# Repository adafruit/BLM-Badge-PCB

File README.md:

# BLM-Badge-PCB

Black Lives Matter interactive electronic learning kit.

https://www.adafruit.com/blacklivesmatter

CAD files are released under Public Domain

https://creativecommons.org/share-your-work/public-domain/

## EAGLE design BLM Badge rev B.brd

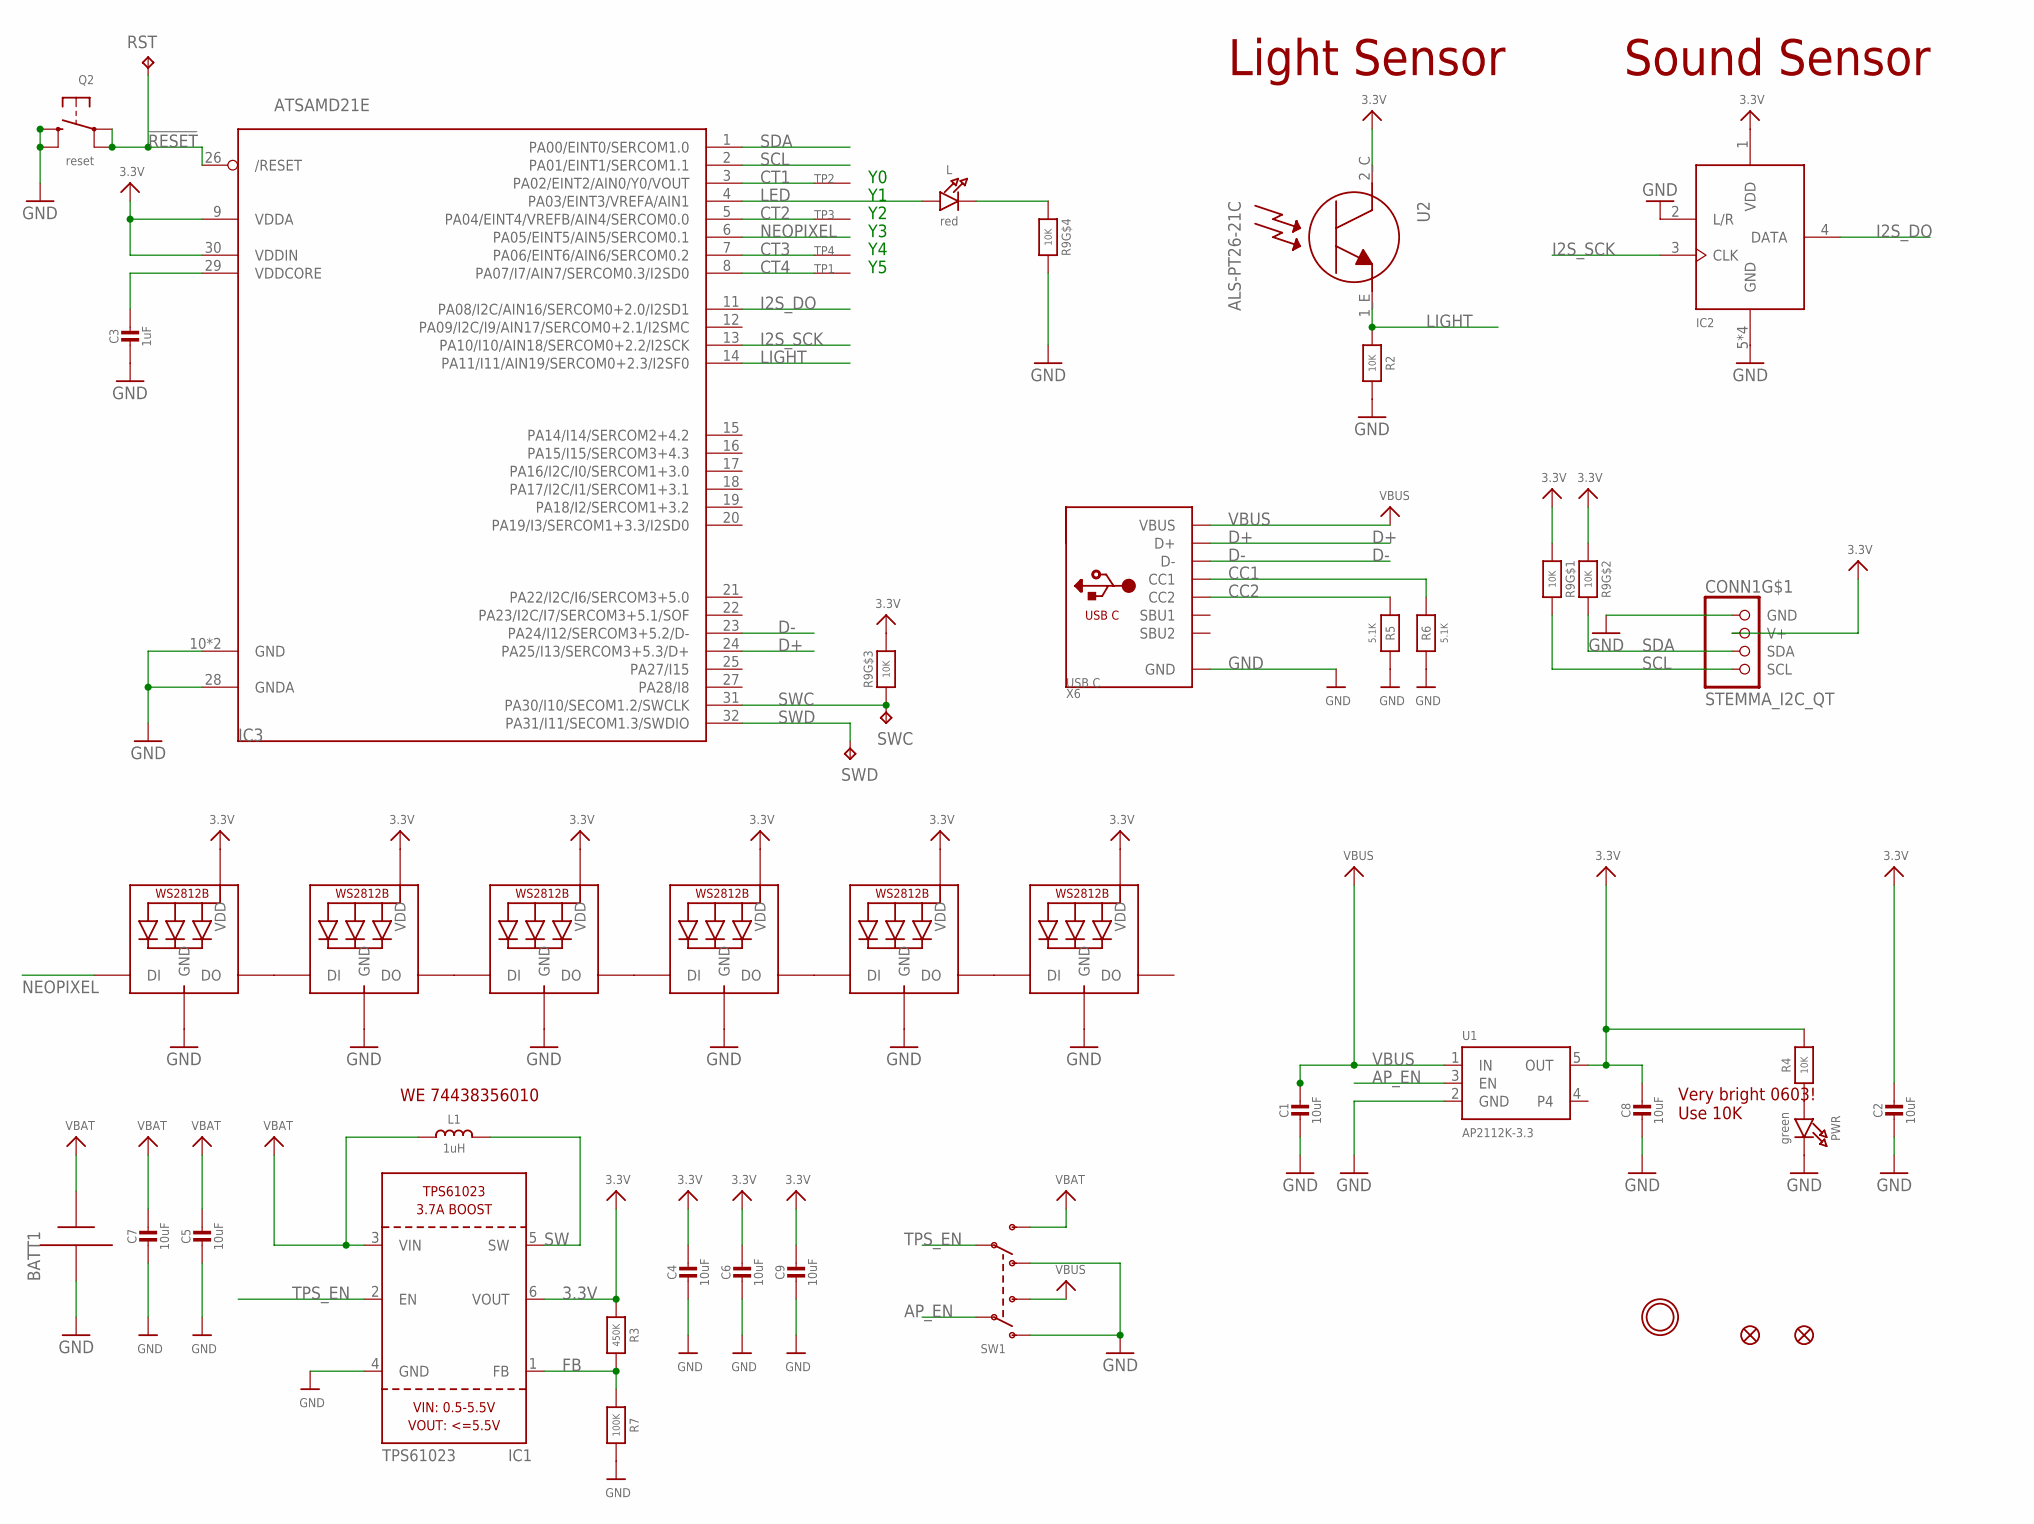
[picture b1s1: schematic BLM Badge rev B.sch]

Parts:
BATT1: BATTERYHOLDER_2XAAA; 2XAAA
C1, C2, C4, C5, C6, C7, C8, C9: 10uF; 0805-NO
C3: 1uF; 0603-NO
CONN1: STEMMA_I2C_QT; JST_SH4
FID1, FID2: FIDUCIAL_1MM
IC1: TPS61023; SOT563
IC2: MIC_PDM; SPK0415HM4H
IC3: ATSAMD21E; QFN32_5MM
L: red; CHIPLED_0603_NOOUTLINE
L1: 1uH; INDUCTOR_5X5MM_TDK_VLC5045
LED2, LED3, LED4, LED5, LED6, LED7: WS2812B_4020
PWR: green; CHIPLED_0603_NOOUTLINE
Q2: reset; BTN_KMR2_4.6X2.8
R2, R4: 10K; 0603-NO
R3: 450K; 0603-NO
R5, R6: 5.1K; 0603-NO
R7: 100K; 0603-NO
R9: 10K; RESPACK_4X0603
RST: TPTP17R; TP17R
SW1: SWITCH_DPDTEG1390; EG1390
SWC: TPTP17R; TP17R
SWD: TPTP17R; TP17R
TP1, TP2, TP3, TP4: SEWTAPPCB_ALLIGATOR; PCB_ALLI
U1: AP2112K-3.3; SOT23-5
U2: ALS-PT26-21C
U$33: MOUNTINGHOLE3.0THIN; MOUNTINGHOLE_3.0_PLATEDTHIN
X6: USB C; USB_C_CUSB31-CFM2AX-01-X

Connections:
3.3V: C2.1, C4.1, C6.1, C8.1, C9.1, CONN1.2 (V+), IC1.6 (VOUT), IC2.1 (VDD), IC3.9 (VDDA), IC3.30 (VDDIN), LED2.2 (VDD), LED3.2 (VDD), LED4.2 (VDD), LED5.2 (VDD), LED6.2 (VDD), LED7.2 (VDD), R3.1, R4.2, R9.1, R9.2 (1), R9.6 (2), U1.5 (OUT), U2.2_C (C)
!RESET: IC3.26 (/RESET), Q2.A, Q2.A' (P1), RST.TP
AP_EN: SW1.P1, U1.3 (EN)
CC1: R6.2, X6.A5 (CC1)
CC2: R5.2, X6.B5 (CC2)
CT1: IC3.3 (PA02/EINT2/AIN0/Y0/VOUT), TP2.P$1
CT2: IC3.5 (PA04/EINT4/VREFB/AIN4/SERCOM0.0), TP3.P$1
CT3: IC3.7 (PA06/EINT6/AIN6/SERCOM0.2), TP4.P$1
CT4: IC3.8 (PA07/I7/AIN7/SERCOM0.3/I2SD0), TP1.P$1
D+: IC3.24 (PA25/I13/SERCOM3+5.3/D+), X6.A6 (D+), X6.B6 (D+)
D-: IC3.23 (PA24/I12/SERCOM3+5.2/D-), X6.A7 (D-), X6.B7 (D-)
FB: IC1.1 (FB), R3.2, R7.1
GND: BATT1.MINUS (-), C1.2, C2.2, C3.2, C4.2, C5.2, C6.2, C7.2, C8.2, C9.2, CONN1.1 (GND), IC1.4 (GND), IC2.2 (L/R), IC2.5 (GND), IC2.6 (GND), IC2.7 (GND), IC2.8 (GND), IC3.10 (GND), IC3.28 (GNDA), IC3.33 (GND), LED2.4 (GND), LED3.4 (GND), LED4.4 (GND), LED5.4 (GND), LED6.4 (GND), LED7.4 (GND), PWR.C, Q2.B (S), Q2.B' (S1), R2.1, R5.1, R6.1, R7.2, R9.5 (2), SW1.O1, SW1.O2, U1.2 (GND), X6.A1B12 (GND), X6.B1A12 (GND)
I2S_DO: IC2.4 (DATA), IC3.11 (PA08/I2C/AIN16/SERCOM0+2.0/I2SD1)
I2S_SCK: IC2.3 (CLK), IC3.13 (PA10/I10/AIN18/SERCOM0+2.2/I2SCK)
LED: IC3.4 (PA03/EINT3/VREFA/AIN1), L.A
LIGHT: IC3.14 (PA11/I11/AIN19/SERCOM0+2.3/I2SF0), R2.2, U2.1_E (E)
unnamed: L.C, R9.4 (1)
unnamed: PWR.A, R4.1
unnamed: LED2.3 (DO), LED3.1 (DI)
unnamed: LED3.3 (DO), LED4.1 (DI)
unnamed: LED4.3 (DO), LED5.1 (DI)
unnamed: LED6.3 (DO), LED7.1 (DI)
unnamed: LED5.3 (DO), LED6.1 (DI)
NEOPIXEL: IC3.6 (PA05/EINT5/AIN5/SERCOM0.1), LED2.1 (DI)
SCL: CONN1.4 (SCL), IC3.2 (PA01/EINT1/SERCOM1.1), R9.8 (2)
SDA: CONN1.3 (SDA), IC3.1 (PA00/EINT0/SERCOM1.0), R9.7 (2)
SW: IC1.5 (SW), L1.P$2 (2)
SWC: IC3.31 (PA30/I10/SECOM1.2/SWCLK), R9.3 (1), SWC.TP
SWD: IC3.32 (PA31/I11/SECOM1.3/SWDIO), SWD.TP
TPS_EN: IC1.2 (EN), SW1.P2
VBAT: BATT1.PLUS (+), C5.1, C7.1, IC1.3 (VIN), L1.P$1 (1), SW1.S2
VBUS: C1.1, SW1.S1, U1.1 (IN), X6.A4B9 (VBUS), X6.B4A9 (VBUS)
VDDCORE: C3.1, IC3.29 (VDDCORE)

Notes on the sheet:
Very bright 0603! Use 10K
WE 74438356010
Sound Sensor
Light Sensor

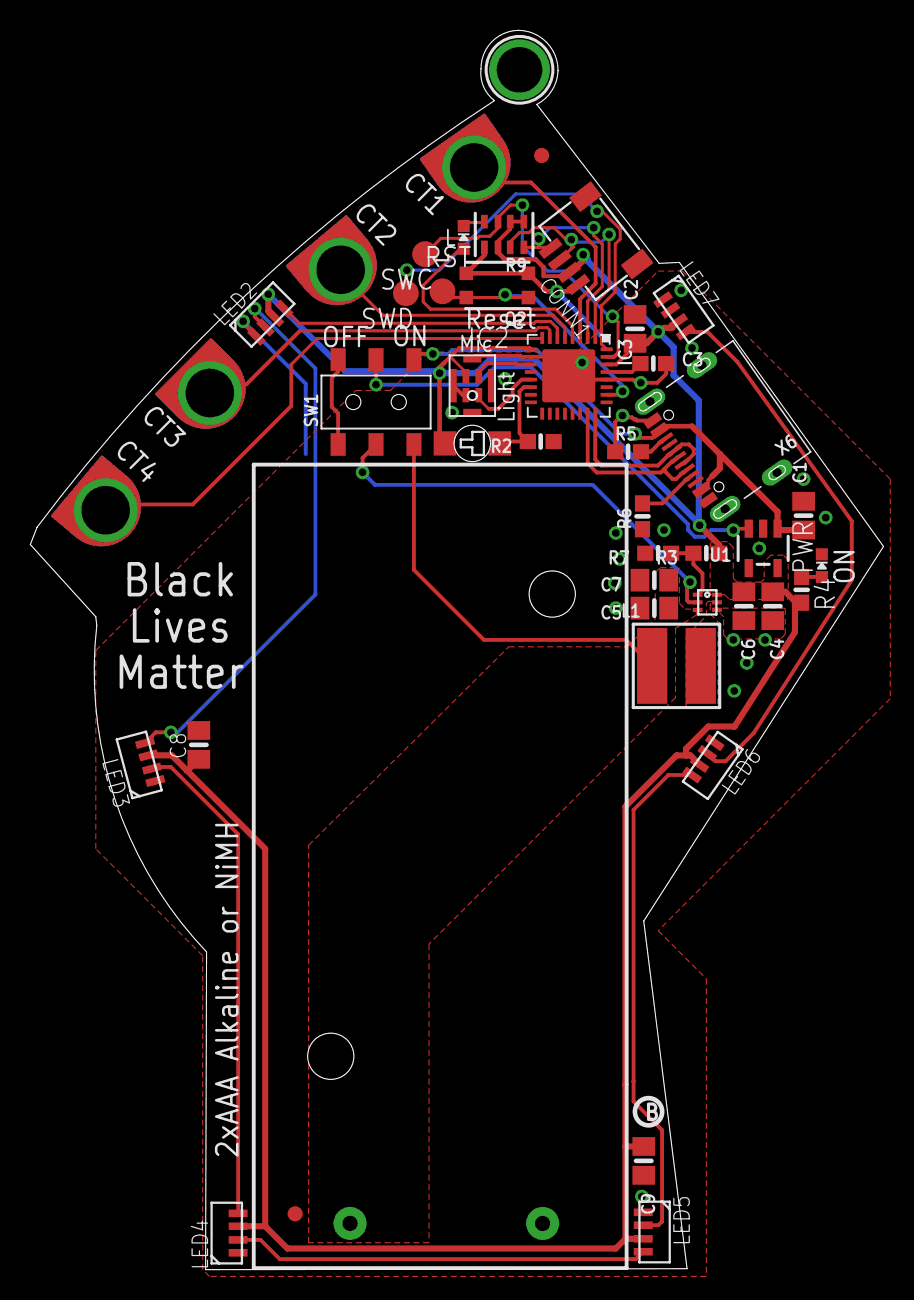
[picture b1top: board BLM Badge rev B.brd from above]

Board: 2 copper layers, 56.3 x 81.7 mm, 47 parts (1 on the bottom side), 34 nets.

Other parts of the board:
U$1: BLM_FRONT
U$40: PCBFEAT-REV-040

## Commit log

2020-08-29 add pcb files
2020-08-29 add text

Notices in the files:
parts and their libraries:
microbuilder: This work is placed in the public domain, and may be freely used for commercial and non-commercial work with the following conditions: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
